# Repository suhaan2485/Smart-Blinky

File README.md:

# Smart-Blinky

This is an Pathfinder Project which will runs leds in such a sequence that it blinks in a coded pattern using a pcb, some buttons and an XIAO RP2040

Softwares used: KiCad, Google Chrome, Arduino(2.3.8) 

Simple PCB which uses some 5mm - LEDs, XIAO RP2040 Arduino, MX Key Switches, generic keycaps and 68ohm resistors.
In my case i will use 3 buttons and 3 leds so 3 of each except the RP2040.

Here is what each button is supposed to do:

Button 1 - Blinks any random LED using random()

Button 2 - L2-(L1+L3) sequence

Button 3 - Complex animation effect

The Arduino Codes can be found in the File named "Arduino Codes" attached in this github repo! 

The Gerber file/s can be found directly in the main branch or "KiCad Files" Folder

# **Photos:**

Schematics:

PCB Layout:

PCB 3D Front View:

PCB 3D Back View:

PCB Front View: 

PCB Back View:

U can also Find The Live Demo of my project in the MP4 linked in this repo!!

Bill Of Material:

| Name | Purpose | Quantity | Total Cost (USD) | Link | Distributor |
|----------|----------|----------|----------|----------|----------|
| Cherry MX2A Switch (10) | Keyboard Switch | 1 | 4.6 | https://meckeys.com/shop/accessories/keyboard-accessories/key-switches/cherry-mx2a-switch/?attribute_pa_cherry-mx=blue-rgb | Mac Keys |
| Blank DSA Keycaps (5) | Keyboard Keycap | 1 | 1.1 | https://meckeys.com/shop/accessories/keyboard-accessories/keycaps/blank/blank-dsa-keycaps-1u/?attribute_pa_variations=off-white | Mac Keys |
| 5mm Blue LED (10) | LED for blink blink o_0 | 1 | 0.25 | https://thinkrobotics.com/products/5mm-led-pack-of-10?variant=12744149205064 | Think Robotics |
| 5mm Green LED (10) | LED for blink blink o_0 | 1 | 0.25 | https://thinkrobotics.com/products/5mm-led-pack-of-10?variant=12744149205064 | Think Robotics |
| 5mm Red LED (10) | LED for blink blink o_0 | 1 | 0.25 | https://thinkrobotics.com/products/5mm-led-pack-of-10?variant=12744149205064 | Think Robotics |
| Seeed Studio XIAO RP2040 | Brain I would say | 1 | 5.8 | https://thinkrobotics.com/products/seeed-studio-xiao-rp2040?variant=47933480173885&country=IN&currency=INR&utm_medium=product_sync&utm_source=google&utm_content=sag_organic&utm_campaign=sag_organic&utm_source=googleads&utm_medium=cpc&utm_source=SR_google&utm_medium=Shopping&utm_campaign=SR467_ShoppingAds_Category-23015774368&utm_content=-293946777986&gad_source=1&gad_campaignid=23015774368&gbraid=0AAAAACk3EvwNg85ivfXz7_douBtysfEe2&gclid=Cj0KCQjwrZTRBhDSARIsAHidYfc42TlNvgxk9vyaR3ITMNI-v1SkI1oklDQBm8kxzEVwLjYCuWwf5FUaAjsrEALw_wcB | Think Robotics |
| 68 Ohm 1/4 Watt Resistor with 1% Tolerance (10) | Resistance for LEDs | 1 | 0.11 | https://quartzcomponents.com/products/68-ohm-1-4-watt-resistor-with-1-tolerance-pack-of-10?variant=45769223897322 | Quatrz Componenets |
| PCB | "Mother"- Board | 1 | 13.55 | https://www.lioncircuits.com/cart | Lion Circuits |

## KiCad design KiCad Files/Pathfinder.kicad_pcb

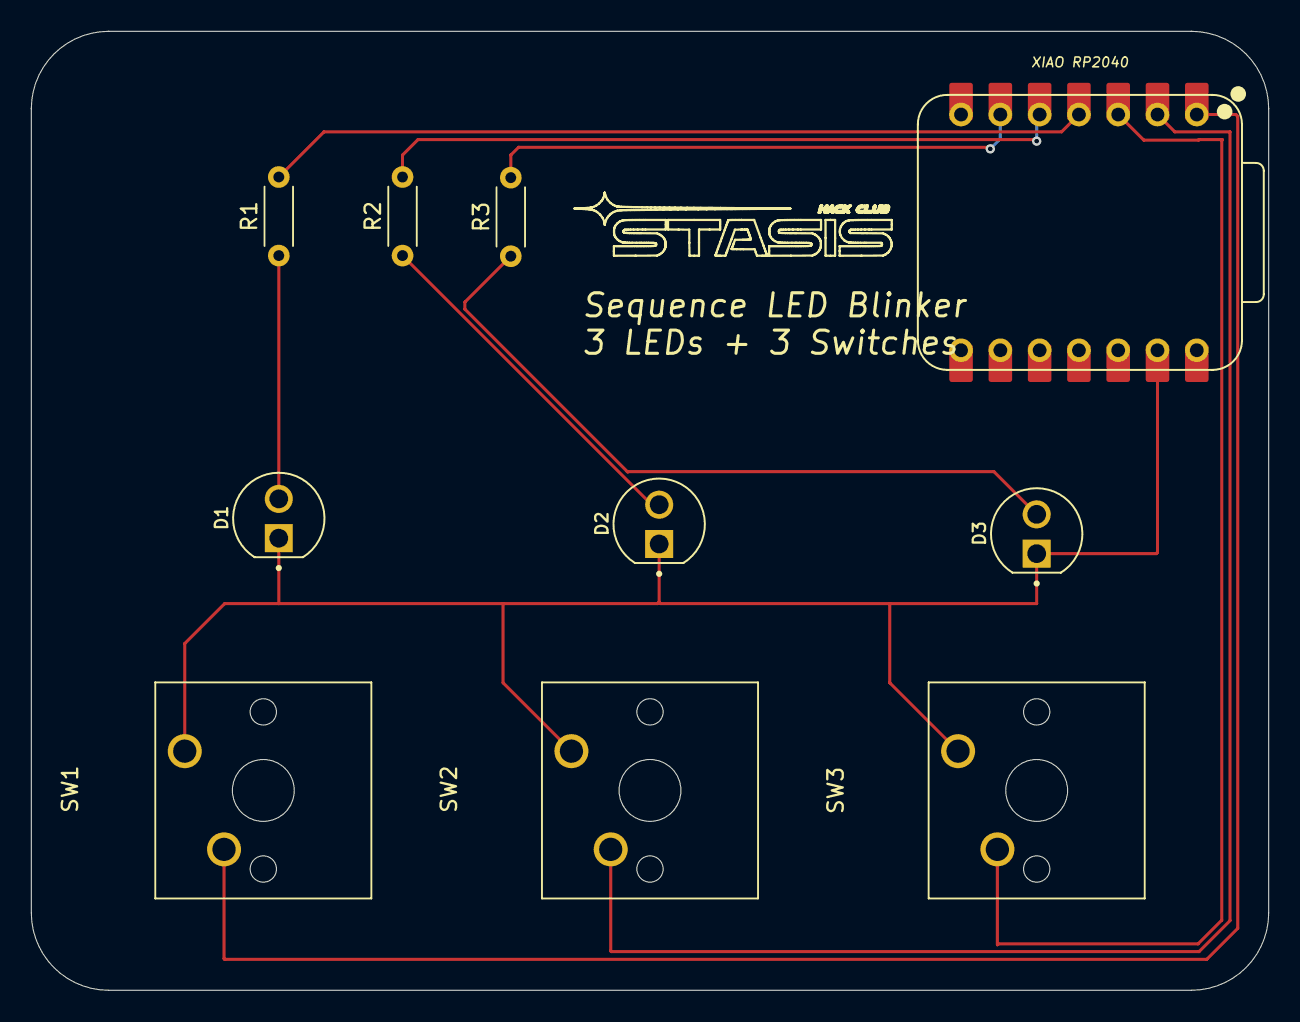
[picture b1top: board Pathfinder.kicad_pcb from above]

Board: 2 copper layers, 80.0 x 62.0 mm, 10 parts (0 on the bottom side), 10 nets.

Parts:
D1, D2, D3: L08R5000Q1; LEDRD254W57D500H1070
R1, R2, R3: R; R_Axial_DIN0204_L3.6mm_D1.6mm_P5.08mm_Horizontal
SW1, SW2, SW3: SW_Push; SW_Cherry_MX_1.00u_PCB
XIAO RP2040: XIAO-RP2040-DIP

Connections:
BT 1: SW1.2, XIAO RP2040.1 (P26_A0_D0)
BT 2: SW2.2, XIAO RP2040.2 (P27_A1_D1)
BT 3: SW3.2, XIAO RP2040.3 (P28_A2_D2)
GND: D1.C, D2.C, D3.C, SW1.1, SW2.1, SW3.1, XIAO RP2040.13 (GND)
LED 1: R1.2, XIAO RP2040.4 (P29_A3_D3)
LED 2: R2.2, XIAO RP2040.5 (P6_SDA_D4)
LED 3: R3.2, XIAO RP2040.6 (P7_SCL_D5)
unnamed: D1.A, R1.1
unnamed: D2.A, R2.1
unnamed: D3.A, R3.1

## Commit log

2026-05-24 Create Arduino Codes
2026-05-27 Update README.md
    Added BOM
2026-06-06 Create random
2026-06-07 Update README.md
    Updated Starting text
    Also mentioned needed components specifically
    Altered some images as pcb has been changesd
2026-06-07 Add files via upload
    Adding KiCad Files
2026-06-07 Create random1
2026-06-07 Add files via upload
    Adding Gerber Fies
2026-06-07 Delete KiCad Files/random
    Delteing Temporary File
2026-06-10 Update README.md
    Added the BOM table in markdown format
2026-06-17 Delete Smart Blinky-bom.csv
    Deleteing Old CSV Files
2026-06-17 Update README.md
    Updating BOM
2026-06-17 Add files via upload
    Uploading BOM
2026-06-18 Moved Photos
2026-06-18 Create PCB Building Photos
2026-06-18 deleted temporary folder
2026-06-25 Improve Arduino code structure and comments
    Refactored Arduino code for clarity and functionality.
    Made the code better
